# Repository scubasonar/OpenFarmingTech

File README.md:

# OpenFarmingTech
Open source farming technologies

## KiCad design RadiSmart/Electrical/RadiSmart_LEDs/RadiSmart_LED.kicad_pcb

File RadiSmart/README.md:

# RadiSmart
Rugged smart light with self-diagnostics

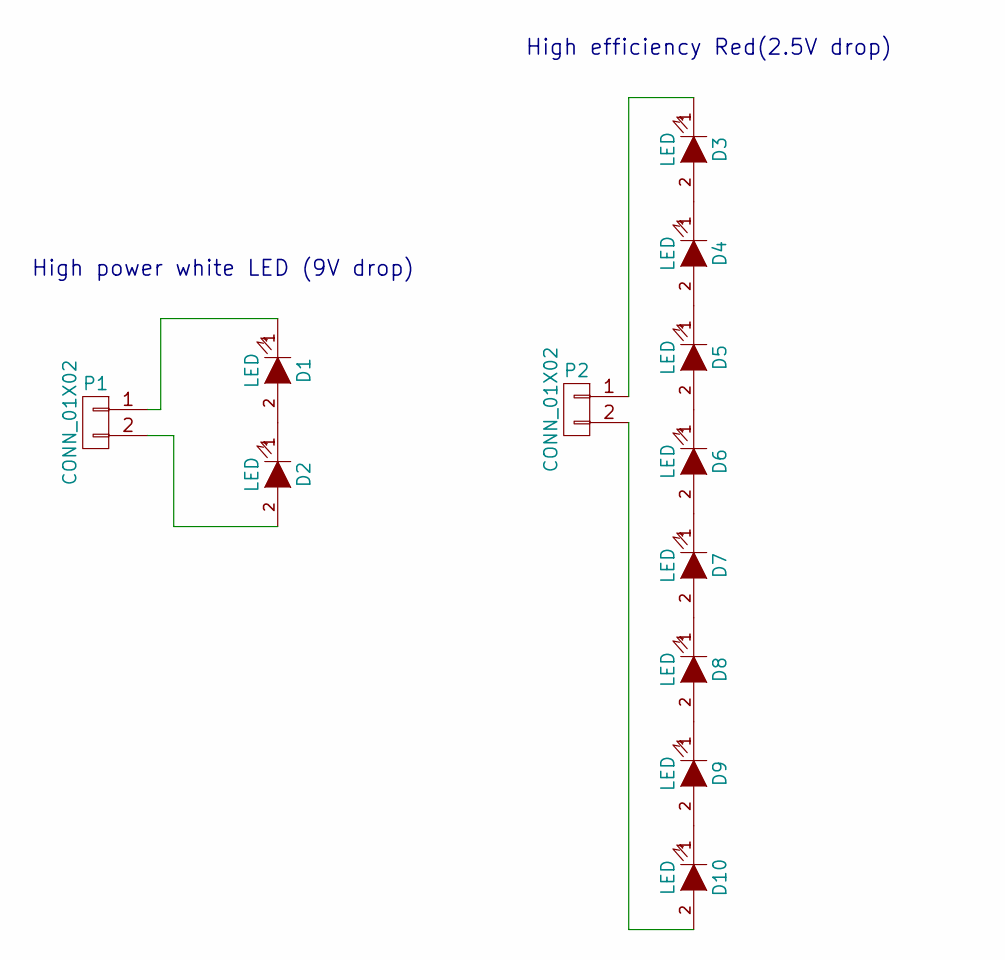
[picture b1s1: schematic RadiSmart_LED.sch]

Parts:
D1, D2: LED; CREE_LED_2020
D3, D4, D5, D6, D7, D8, D9, D10: LED; CREE-LED-XP-E
P1, P2: CONN_01X02; CONN-2-503471-0200

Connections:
unnamed: D1.1 (K), P1.1
unnamed: D1.2 (A), D2.1 (K)
unnamed: D2.2 (A), P1.2
unnamed: D3.1 (K), P2.1
unnamed: D3.2 (A), D4.1 (K)
unnamed: D4.2 (A), D5.1 (K)
unnamed: D5.2 (A), D6.1 (K)
unnamed: D6.2 (A), D7.1 (K)
unnamed: D7.2 (A), D8.1 (K)
unnamed: D8.2 (A), D9.1 (K)
unnamed: D9.2 (A), D10.1 (K)
unnamed: D10.2 (A), P2.2

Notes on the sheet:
High power white LED (9V drop)
High efficiency Red(2.5V drop)

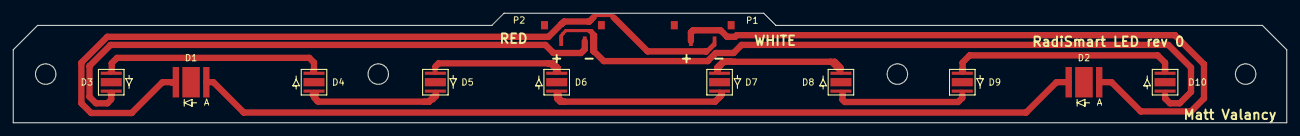
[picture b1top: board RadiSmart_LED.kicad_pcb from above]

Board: 2 copper layers, 199.4 x 17.1 mm, 12 parts (0 on the bottom side), 12 nets.

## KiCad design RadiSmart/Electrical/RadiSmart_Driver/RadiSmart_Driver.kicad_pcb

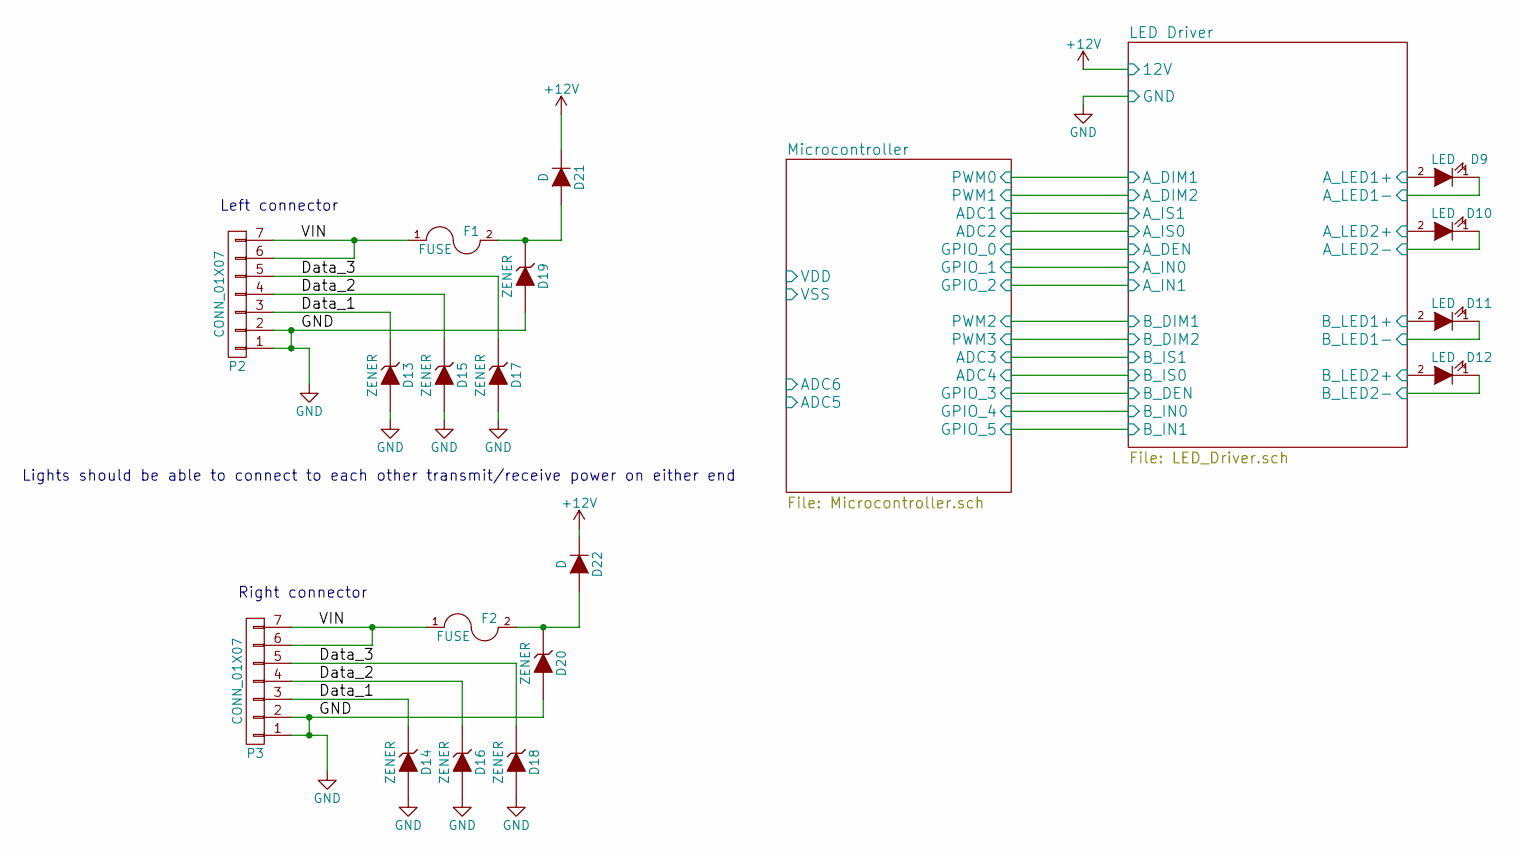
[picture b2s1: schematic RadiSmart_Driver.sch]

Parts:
D9, D10, D11, D12: LED; CREE_LED_2020
D13, D14, D15, D16, D17, D18, D19, D20: ZENER; SMA_Standard
D21, D22: D; DD-PAK_TO263_SingleDiode
F1, F2: FUSE; Fuse_SMD1206_HandSoldering
P2, P3: CONN_01X07; Pin_Header_Straight_1x07

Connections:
+12V: D21.1 (K), D22.1 (K); also elsewhere on the board
/Data_1: D13.1 (K), D14.1 (K), P2.3, P3.3
/Data_2: D15.1 (K), D16.1 (K), P2.4, P3.4
/Data_3: D17.1 (K), D18.1 (K), P2.5, P3.5
/LED Driver/A_LED1+: D9.2 (A); also elsewhere on the board
/LED Driver/A_LED1-: D9.1 (K); also elsewhere on the board
/LED Driver/A_LED2+: D10.2 (A); also elsewhere on the board
/LED Driver/A_LED2-: D10.1 (K); also elsewhere on the board
/LED Driver/B_LED1+: D11.2 (A); also elsewhere on the board
/LED Driver/B_LED1-: D11.1 (K); also elsewhere on the board
/LED Driver/B_LED2+: D12.2 (A); also elsewhere on the board
/LED Driver/B_LED2-: D12.1 (K); also elsewhere on the board
/VIN: F1.1, F2.1, P2.6, P2.7, P3.6, P3.7
GND: D13.2 (A), D14.2 (A), D15.2 (A), D16.2 (A), D17.2 (A), D18.2 (A), D19.2 (A), D20.2 (A), P2.1, P2.2, P3.1, P3.2; also elsewhere on the board
unnamed: D19.1 (K), D21.2 (A), F1.2
unnamed: D20.1 (K), D22.2 (A), F2.2

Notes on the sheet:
Left connector
Right connector
Lights should be able to connect to each other transmit/receive power on either end

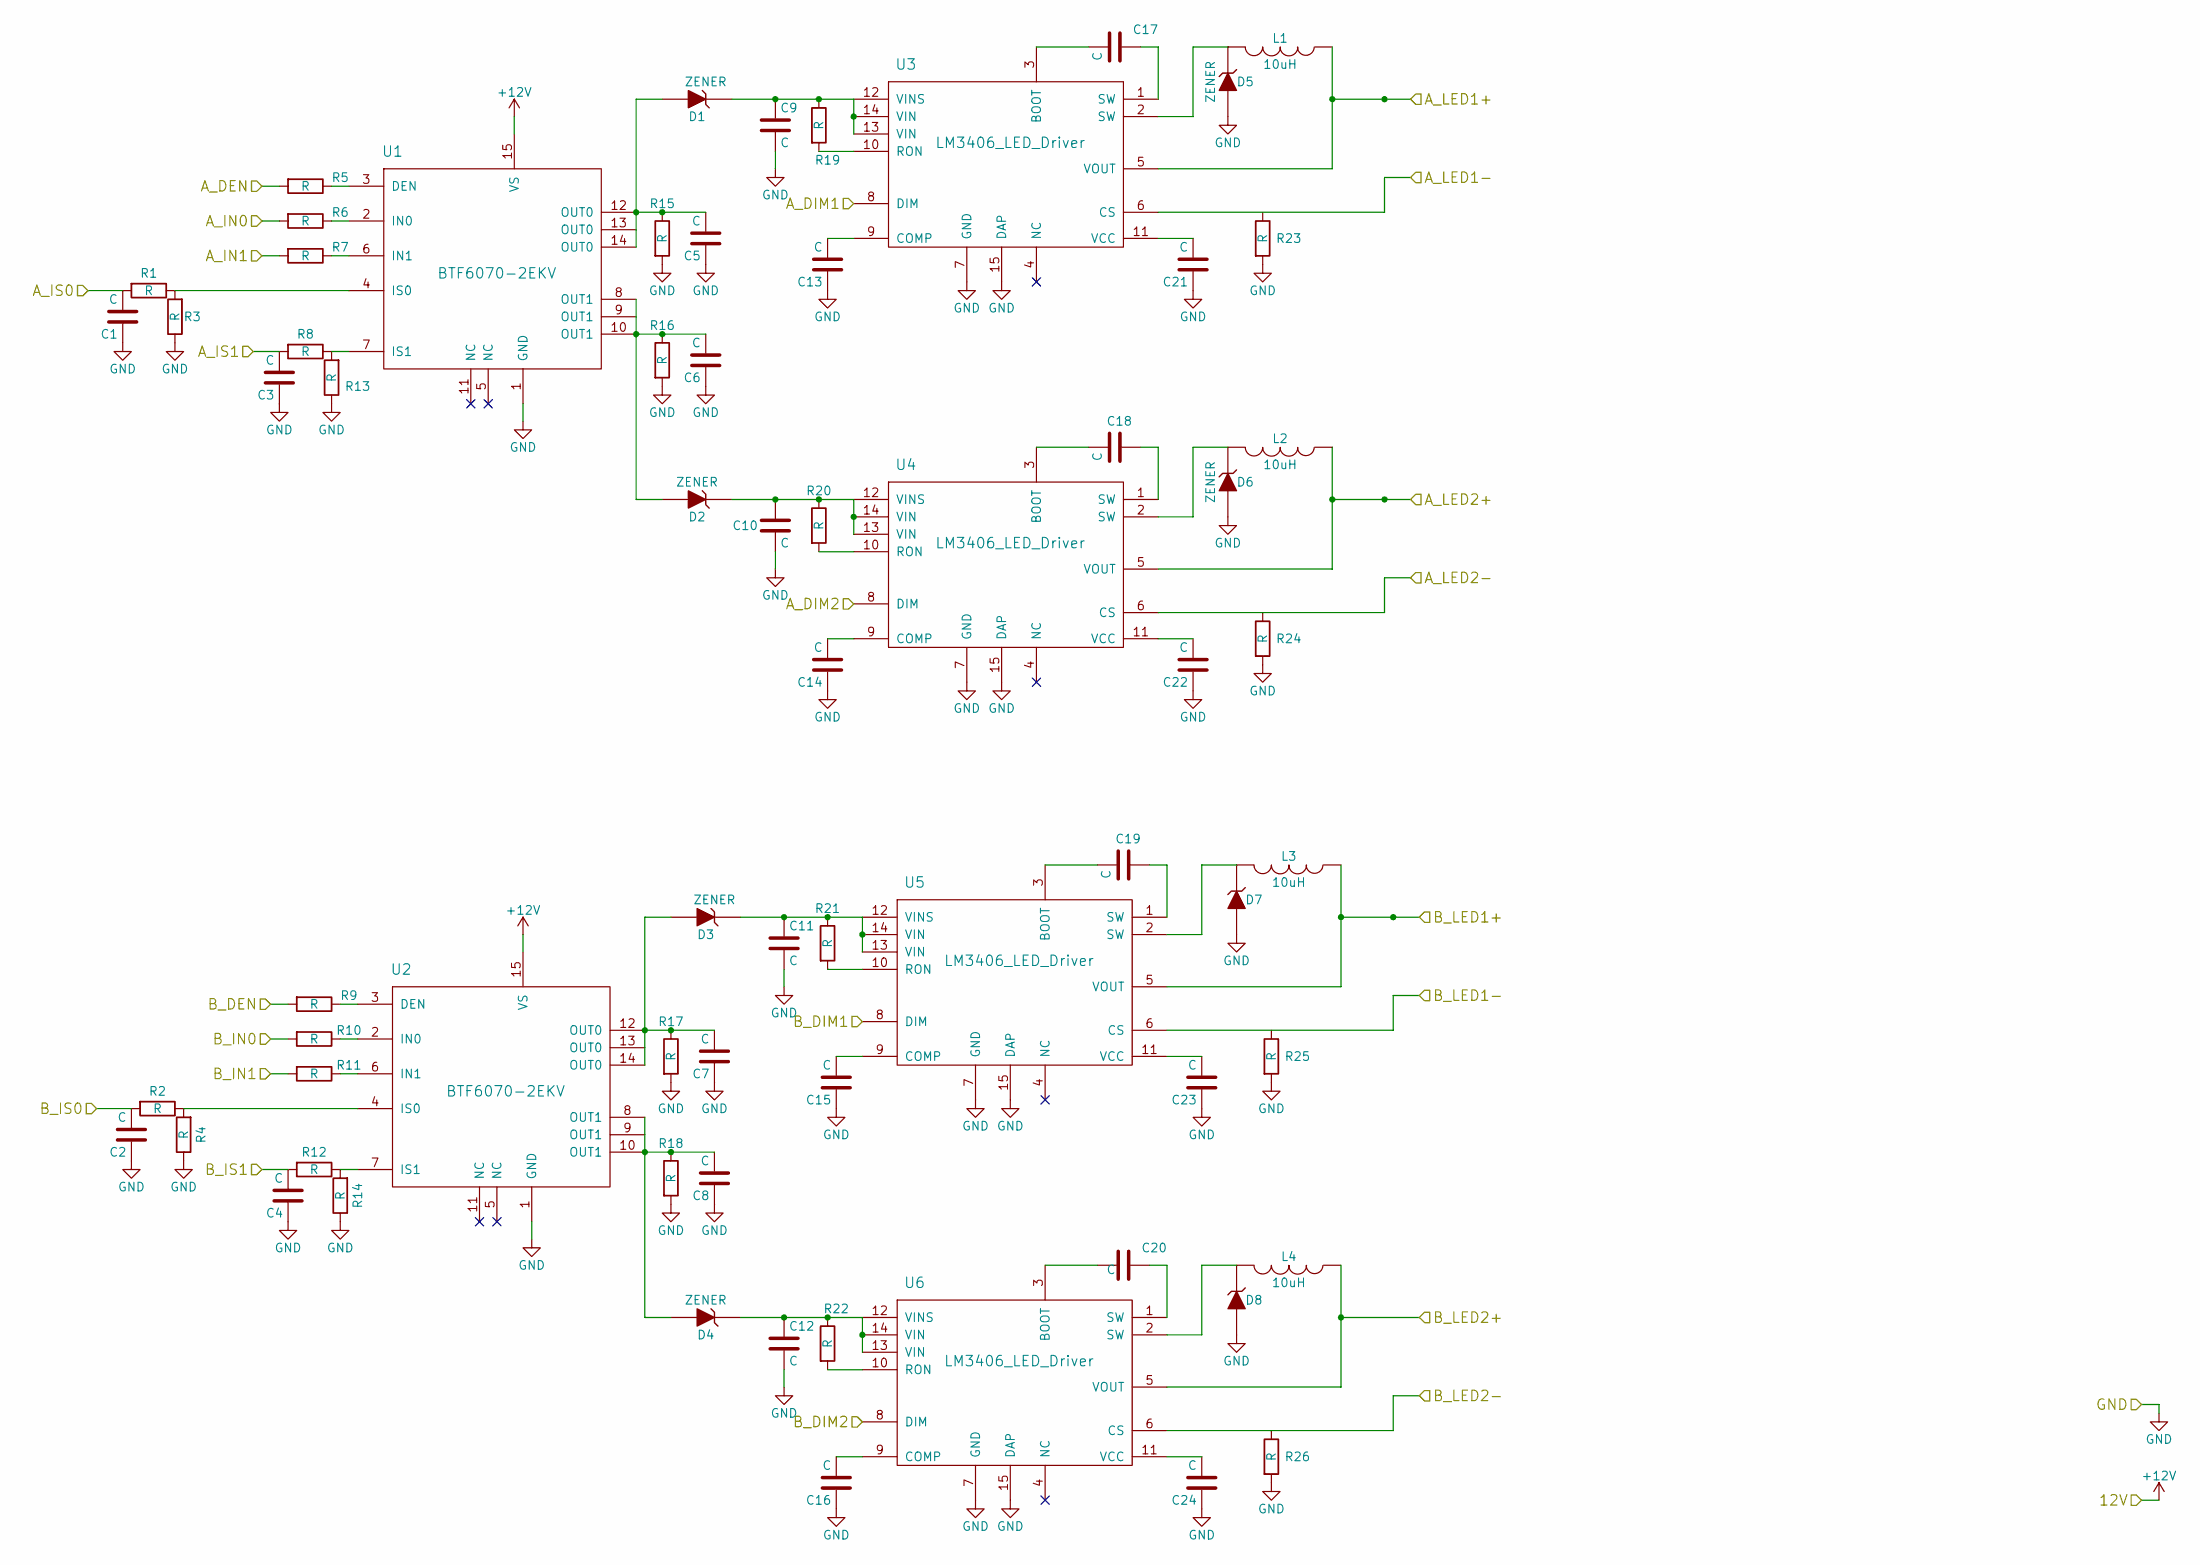
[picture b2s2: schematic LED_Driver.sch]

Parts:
C1, C2, C3, C4, C5, C6, C7, C8, C9, C10, C11, C12, C13, C14, C15, C16, C17, C18, C19, C20, C21, C22, C23, C24: C; C_0805
D1, D2, D3, D4, D5, D6, D7, D8: ZENER; SMA_Standard
L1, L2, L3, L4: 10uH; IND_HCM1A0703-100-R; MFG PN HCM1A0703-100-R
R1, R2, R3, R4, R5, R6, R7, R8, R9, R10, R11, R12, R13, R14, R15, R16, R17, R18, R19, R20, R21, R22, R23, R24, R25, R26: R; R_0805
U1, U2: BTF6070-2EKV; PG-DSO-14-40_EP
U3, U4, U5, U6: LM3406_LED_Driver; 14-TSSOP-PWP0014G

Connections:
+12V: U1.15 (VS), U2.15 (VS); also elsewhere on the board
/LED Driver/A_DEN: R5.2; also elsewhere on the board
/LED Driver/A_DIM1: U3.8 (DIM); also elsewhere on the board
/LED Driver/A_DIM2: U4.8 (DIM); also elsewhere on the board
/LED Driver/A_IN0: R6.2; also elsewhere on the board
/LED Driver/A_IN1: R7.2; also elsewhere on the board
/LED Driver/A_LED1+: L1.1, U3.5 (VOUT); also elsewhere on the board
/LED Driver/A_LED1-: U3.6 (CS); also elsewhere on the board
/LED Driver/A_LED2+: L2.1, U4.5 (VOUT); also elsewhere on the board
/LED Driver/A_LED2-: U4.6 (CS); also elsewhere on the board
/LED Driver/B_DEN: R9.2; also elsewhere on the board
/LED Driver/B_DIM1: U5.8 (DIM); also elsewhere on the board
/LED Driver/B_DIM2: U6.8 (DIM); also elsewhere on the board
/LED Driver/B_IN0: R10.2; also elsewhere on the board
/LED Driver/B_IN1: R11.2; also elsewhere on the board
/LED Driver/B_LED1+: L3.1, U5.5 (VOUT); also elsewhere on the board
/LED Driver/B_LED1-: U5.6 (CS); also elsewhere on the board
/LED Driver/B_LED2+: L4.1, U6.5 (VOUT); also elsewhere on the board
/LED Driver/B_LED2-: U6.6 (CS); also elsewhere on the board
/Microcontroller/ADC1: C3.2, R8.2; also elsewhere on the board
/Microcontroller/ADC2: C1.2, R1.2; also elsewhere on the board
/Microcontroller/ADC3: C4.2, R12.2; also elsewhere on the board
/Microcontroller/ADC4: C2.2, R2.2; also elsewhere on the board
GND: C1.1, C2.1, C3.1, C4.1, C5.1, C6.1, C7.1, C8.1, C9.2, C10.2, C11.2, C12.2, C13.1, C14.1, C15.1, C16.1, C21.1, C22.1, C23.1, C24.1, D5.2 (A), D6.2 (A), D7.2 (A), D8.2 (A), R3.1, R4.1, R13.1, R14.1, R15.2, R16.2, R17.2, R18.2, R23.2, R24.2, R25.2, R26.2, U1.1 (GND), U2.1 (GND), U3.7 (GND), U3.15 (DAP), U4.7 (GND), U4.15 (DAP), U5.7 (GND), U5.15 (DAP), U6.7 (GND), U6.15 (DAP); also elsewhere on the board
unnamed: C5.2, D1.2 (A), R15.1, U1.12 (OUT0), U1.14 (OUT0)
unnamed: C6.2, D2.2 (A), R16.1, U1.8 (OUT1), U1.10 (OUT1)
unnamed: C7.2, D3.2 (A), R17.1, U2.12 (OUT0), U2.14 (OUT0)
unnamed: C8.2, D4.2 (A), R18.1, U2.8 (OUT1), U2.10 (OUT1)
unnamed: C9.1, D1.1 (K), R19.1, U3.12 (VINS), U3.13 (VIN), U3.14 (VIN)
unnamed: C10.1, D2.1 (K), R20.1, U4.12 (VINS), U4.13 (VIN), U4.14 (VIN)
unnamed: C11.1, D3.1 (K), R21.1, U5.12 (VINS), U5.13 (VIN), U5.14 (VIN)
unnamed: C12.1, D4.1 (K), R22.1, U6.12 (VINS), U6.13 (VIN), U6.14 (VIN)
unnamed: C13.2, U3.9 (COMP)
unnamed: C14.2, U4.9 (COMP)
unnamed: C15.2, U5.9 (COMP)
unnamed: C16.2, U6.9 (COMP)
unnamed: C17.1, U3.1 (SW)
unnamed: C17.2, U3.3 (BOOT)
unnamed: C18.1, U4.1 (SW)
unnamed: C18.2, U4.3 (BOOT)
unnamed: C19.1, U5.1 (SW)
unnamed: C19.2, U5.3 (BOOT)
unnamed: C20.1, U6.1 (SW)
unnamed: C20.2, U6.3 (BOOT)
unnamed: C21.2, U3.11 (VCC)
unnamed: C22.2, U4.11 (VCC)
unnamed: C23.2, U5.11 (VCC)
unnamed: C24.2, U6.11 (VCC)
unnamed: D5.1 (K), L1.2, U3.2 (SW)
unnamed: D6.1 (K), L2.2, U4.2 (SW)
unnamed: D7.1 (K), L3.2, U5.2 (SW)
unnamed: D8.1 (K), L4.2, U6.2 (SW)
unnamed: R1.1, R3.2, U1.4 (IS0)
unnamed: R2.1, R4.2, U2.4 (IS0)
unnamed: R5.1, U1.3 (DEN)
unnamed: R6.1, U1.2 (IN0)
unnamed: R7.1, U1.6 (IN1)
unnamed: R9.1, U2.3 (DEN)
unnamed: R10.1, U2.2 (IN0)
unnamed: R11.1, U2.6 (IN1)
unnamed: R12.1, R14.2, U2.7 (IS1)
unnamed: R8.1, R13.2, U1.7 (IS1)
unnamed: R19.2, U3.10 (RON)
unnamed: R20.2, U4.10 (RON)
unnamed: R21.2, U5.10 (RON)
unnamed: R22.2, U6.10 (RON)

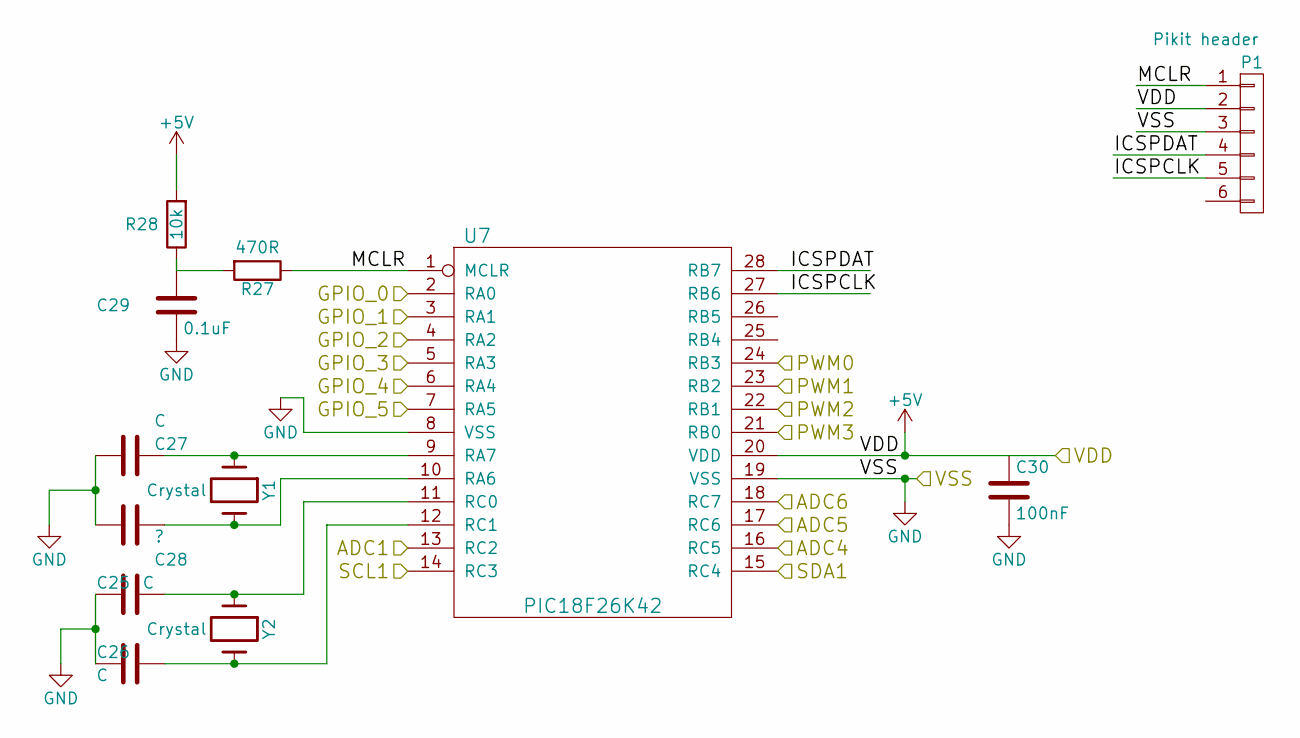
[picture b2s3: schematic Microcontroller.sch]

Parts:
C25, C26, C27: C; C_0805
C28: ?; C_0805
C29: 0.1uF; C_0805
C30: 100nF; C_0805
P1: Pikit header; Pin_Header_Straight_1x06
R27: 470R; R_0805
R28: 10k; R_0805
U7: PIC18F26K42; SOIC-28
Y1, Y2: Crystal; Crystal_Watch

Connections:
+5V: P1.2, R28.2, U7.20 (VDD)
/LED Driver/A_DEN: U7.2 (RA0); also elsewhere on the board
/LED Driver/A_DIM1: U7.24 (RB3); also elsewhere on the board
/LED Driver/A_DIM2: U7.23 (RB2); also elsewhere on the board
/LED Driver/A_IN0: U7.3 (RA1); also elsewhere on the board
/LED Driver/A_IN1: U7.4 (RA2); also elsewhere on the board
/LED Driver/B_DEN: U7.5 (RA3); also elsewhere on the board
/LED Driver/B_DIM1: U7.22 (RB1); also elsewhere on the board
/LED Driver/B_DIM2: U7.21 (RB0); also elsewhere on the board
/LED Driver/B_IN0: U7.6 (RA4); also elsewhere on the board
/LED Driver/B_IN1: U7.7 (RA5); also elsewhere on the board
/Microcontroller/ADC1: U7.13 (RC2); also elsewhere on the board
/Microcontroller/ADC2: U7.14 (RC3); also elsewhere on the board
/Microcontroller/ADC3: U7.15 (RC4); also elsewhere on the board
/Microcontroller/ADC4: U7.16 (RC5); also elsewhere on the board
/Microcontroller/ADC5: U7.17 (RC6)
/Microcontroller/ADC6: U7.18 (RC7)
/Microcontroller/ICSPCLK: P1.5, U7.27 (RB6)
/Microcontroller/ICSPDAT: P1.4, U7.28 (RB7)
/Microcontroller/MCLR: P1.1, R27.1, U7.1 (MCLR)
GND: C25.2, C26.2, C27.2, C28.2, C29.2, C30.2, P1.3, U7.8 (VSS), U7.19 (VSS); also elsewhere on the board
unnamed: C25.1, U7.11 (RC0), Y2.1
unnamed: C26.1, U7.12 (RC1), Y2.2
unnamed: C27.1, U7.9 (RA7), Y1.1
unnamed: C28.1, U7.10 (RA6), Y1.2
unnamed: C29.1, R27.2, R28.1

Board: 2 copper layers, 98 parts (0 on the bottom side), 81 nets, no tracks yet.

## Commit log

2017-10-26 start of project
2017-11-01 making progress on light PCB
2017-11-01 added datasheets for light PCB
2017-11-06 start of source code
2017-11-06 added placeholder folders and lm3406 samples
2017-11-06 added place holders
2017-11-08 added more datasheets for interesting chips, temperature sensing and real-time clock
2017-11-08 renamed some datasheets for clarity
2017-11-08 place holder folder for tree shaker
2017-11-10 switching from 12V to 24V to support more LEDs per channel
2017-11-10 led board looks OK
2017-11-10 added image
2017-11-10 chunked up traces on led board and generated new gerbers
2017-11-10 sending light pcb out to fab
